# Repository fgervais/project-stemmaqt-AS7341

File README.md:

# AS7341 Stemma QT Board

## OSHPark

<a href="https://oshpark.com/shared_projects/QLaodyIa" target="_blank">https://oshpark.com/shared_projects/QLaodyIa</a>

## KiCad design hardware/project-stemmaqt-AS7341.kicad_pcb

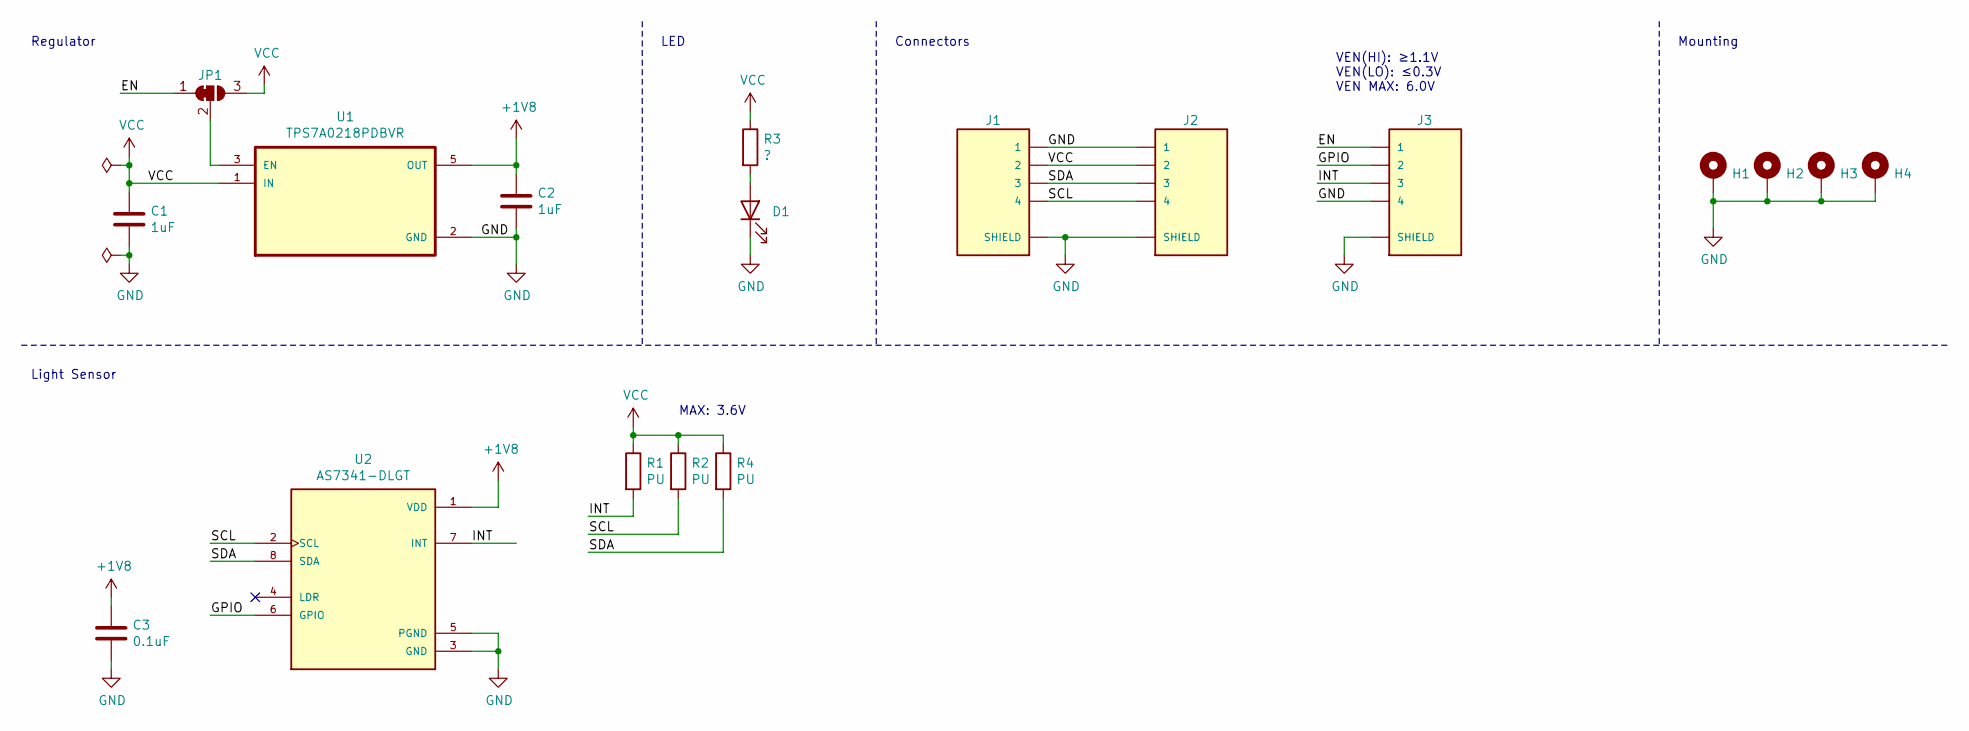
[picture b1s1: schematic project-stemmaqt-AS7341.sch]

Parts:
C1, C2: 1uF; C_0805_2012Metric
C3: 0.1uF; C_0603_1608Metric
D1: LED; LED_0603_1608Metric
H1, H2, H3, H4: MountingHole_Pad; MountingHole_2.2mm_M2_ISO7380_Pad
J1, J2, J3: SM04B-SRSS-TB(LF)(SN); JST_SM04B-SRSS-TB(LF)(SN)
JP1: SolderJumper_3_Bridged12; SolderJumper-3_P1.3mm_Bridged12_RoundedPad1.0x1.5mm
R1, R2, R4: PU; R_0603_1608Metric
R3: ?; R_0603_1608Metric
U1: TPS7A0218PDBVR; SOT95P280X145-5N
U2: AS7341-DLGT; PSON80P310X200X110-8N; PARTREV V3

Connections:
+1V8: C2.1, C3.1, U1.5 (OUT), U2.1 (VDD)
/EN: J3.1, JP1.1 (A)
/GPIO: J3.2, U2.6 (GPIO)
/INT: J3.3, R1.2, U2.7 (INT)
/SCL: J1.4, J2.4, R2.2, U2.2 (SCL)
/SDA: J1.3, J2.3, R4.2, U2.8 (SDA)
GND: C1.2, C2.2, C3.2, D1.1 (K), H1.1, H2.1, H3.1, H4.1, J1.1, J1.S1 (SHIELD), J1.S2 (SHIELD), J2.1, J2.S1 (SHIELD), J2.S2 (SHIELD), J3.4, J3.S1 (SHIELD), J3.S2 (SHIELD), U1.2 (GND), U2.3 (GND), U2.5 (PGND)
unnamed: D1.2 (A), R3.2
unnamed: JP1.2 (C), U1.3 (EN)
VCC: C1.1, J1.2, J2.2, JP1.3 (B), R1.1, R2.1, R3.1, R4.1, U1.1 (IN)

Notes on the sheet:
LED
Connectors
Mounting
Regulator
VEN(HI): ≥1.1V VEN(LO): ≤0.3V VEN MAX: 6.0V
Light Sensor
MAX: 3.6V

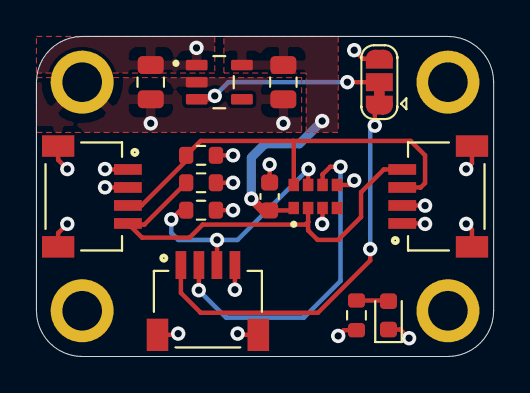
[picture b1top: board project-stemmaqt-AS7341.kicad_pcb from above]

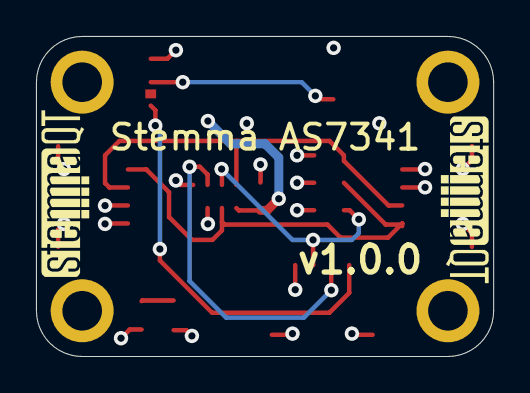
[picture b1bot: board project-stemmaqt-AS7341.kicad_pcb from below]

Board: 4 copper layers, 25.4 x 17.8 mm, 20 parts (2 on the bottom side), 10 nets.

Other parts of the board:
U$30, U$31: STEMMAQT

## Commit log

2022-04-02 Empty README
2022-04-02 Rename PCB project files
2022-04-02 Update library module
2022-04-02 Update schematic for AS7341
2022-04-02 Change regulator to TPS7A0218PDBVR
    Although use TPS7A0233PDBVR symbol and footprint.
2022-04-02 First placement
2022-04-02 Routing done
2022-04-03 Remove 2 files from base project
2022-05-08 Change library submodule url to https
